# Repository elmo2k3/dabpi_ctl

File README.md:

# dabpi_ctl - RPi fm/fmhd/dab receiver control interface

![Image of DABPi+ v11 PCB]
(https://github.com/elmo2k3/dabpi_ctl/blob/master/doc/pics/dabpi+_v11.jpg)
DABPi+ for Raspberry Pi A+/B+ versions. Pi2 not tested yet.
![Image of DABPi v1 PCB]
(https://github.com/elmo2k3/dabpi_ctl/blob/master/doc/pics/dabpi_v1.jpg)
DABPi for older Raspberry Pi A/B versions.

## News

12.4.2015
Works on Pi2 now. New Kernel 3.18.11-v7+ included for Pi2.

## Warning

!!! Firmware files removed due to license issues !!!

This project is beta. A lot of features are still missing.

## Requirements

You need a RPi that has the option to mount the I2S extension header.
![Image of RPi with soldered I2S extension header]
(https://github.com/elmo2k3/dabpi_ctl/blob/master/doc/pics/IMG_0292.JPG)

Get the firmware package for Si4688 from Silabs.

Be sure to enable SPI in raspi-config.

Install wiringPi library. See http://wiringpi.com/download-and-install/

To get the audio you need to install a new kernel. It can be compiled from here
https://github.com/elmo2k3/linux or use the precompiled image. For the precompiled binarys, see the Install section.

## RPi A+/B+ instructions
![Image of RPi B+ with additional cables]
(https://github.com/elmo2k3/dabpi_ctl/blob/master/doc/pics/a_b_plus.jpg)

Connect P5 header pins 3,4,5 to GPIO header pins 12,35,38.

## Install

There is a very simple install script for a fresh raspian now (where there is nothing to be damaged).

```bash
wget https://github.com/elmo2k3/dabpi_ctl/raw/master/install_on_fresh_raspbian.sh
chmod a+x install_on_fresh_raspbian.sh
./install_on_fresh_raspbian.sh
```
This will install the commandline tool to /home/pi/dabpi_ctl

Unpack the firmware files (get it from silabs or ask me) into /home/pi/dabpi_ctl/firmware

### Manual Install

Get and compile the source code:

```bash
git clone https://github.com/elmo2k3/dabpi_ctl
cd dabpi_ctl
make
```
If you want to use the precompiled kernel, it can be found in the kernel/ directory.

```bash
sudo cp kernel/Image /boot/kernel.img
sudo rm -rf /lib/modules
sudo rm -rf /lib/firmware
sudo tar -C / -xvzf kernel/lib.tar.gz
```
Edit /etc/modules
```bash
bcm2708_dmaengine
snd-bcm2835
```
After a reboot load the module.

```bash
sudo modprobe snd-soc-rpi-dabpi
```
You should see this in the kernel log:
```bash
pi@raspberrypi ~/dabpi_ctl $ dmesg | tail -n1
[ 2435.067966] snd-dabpi snd-dabpi.0:  si468x-hifi <-> bcm2708-i2s.0 mapping ok
pi@raspberrypi ~/dabpi_ctl $
```

## Usage

Run dabpi_ctl:

```bash
[bjoern@x200 user_program]$ ./dabpi_ctl
usage: ./dabpi_ctl [-a|-b]
  -a             init DAB mode
  -b             init fm mode
  -c frequency   tune frequency in FM mode
  -d             fm status
  -e             dab status
  -f service     start service of dab service list
  -g             get dab service list
  -i channel     tune to channel in dab frequency list
  -j region      set frequency list
                    0   Baden-Wuertemberg
                    1   Bayern
                    2   Berlin-Brandenburg
                    3   Bremen
                    4   Hamburg
                    5   Hessen
                    6   Mecklenburg-Vorpommern
                    7   Niedersachsen
                    8   Nordrhein-Westfalen
                    9   Rheinland-Pfalz
                    10  Saarland
                    11  Sachsen
                    12  Sachsen-Anhalt
                    13  Schleswig-Holstein
                    14  Thueringen
                    15  Suedtirol (Italien)
                    16  Schweiz
  -k region      scan frequency list
  -l up|down     fm seek next station
  -m             fm rds status
  -n             dab get audio info
  -o             dab get subchannel info
  -s             get sys state (fm,dab,am...)
  -h             this help
```

### Audio output

To test audio output, redirect it from capture to playback device:

```bash
alsaloop -C hw:1,0
```
Stream audio to another linux machine over ssh:

```bash
ssh pi@PI-IP-ADDRESS 'arecord -D hw:1,0 -f dat -' | aplay -f dat -
```

### Examples

Enter fm mode:

```bash
pi@raspberrypi ~/dabpi_ctl $ sudo ./dabpi_ctl -b
si46xx_init_mode_fm()
si46xx_get_sys_state answer: 800000c001ff
si46xx_get_part_info answer: 800000c0000000005012000000005012000000000100
[...]
si46xx_fm_tune_freq(98500)
808000c0
pi@raspberrypi ~/dabpi_ctl $
```

Tune to radio station 106.700MHz:

```bash
pi@raspberrypi ~/dabpi_ctl $ sudo ./dabpi_ctl -c 106700
si46xx_fm_tune_freq(106700)
808000c0
pi@raspberrypi ~/dabpi_ctl $
```

Enter DAB mode and scan all channels in the list for NRW:

```bash
pi@raspberrypi ~/dabpi_ctl $ sudo ./dabpi_ctl -a -k 8
si46xx_init_mode_dab()
[...]
si46xx_dab_tune_freq(0): 818000c0
si46xx_dab_digrad_status(): Channel 0: ACQ: 1 RSSI: 45 SNR: -10 Name: DR Deutschland
si46xx_dab_tune_freq(1): 818000c0
si46xx_dab_digrad_status(): Channel 1: ACQ: 1 RSSI: 41 SNR: -10 Name: Radio fuer NRW
pi@raspberrypi ~/dabpi_ctl $
```

Select DAB channel:

```bash
pi@raspberrypi ~/dabpi_ctl $ sudo ./dabpi_ctl -i 1
si46xx_dab_tune_freq(0): 818000c0
pi@raspberrypi ~/dabpi_ctl $
```

Get ensemble information:

```bash
pi@raspberrypi ~/dabpi_ctl $ sudo ./dabpi_ctl -g
si46xx_dab_get_digital_service_list()
List size:     370
List version:  227
Services:      13
Num:  0  Service ID: e0d01005  Service Name: WDR-INFO          Component ID: 49162
                                                               Component ID: 49162
Num:  1  Service ID:     109d  Service Name: Domradio          Component ID: 12
                                                               Component ID: 0
Num:  2  Service ID: e0d01006  Service Name: WDR-TPEG          Component ID: 49163
                                                               Component ID: 0
Num:  3  Service ID:     d394  Service Name: WDR 4             Component ID: 14
                                                               Component ID: 0
Num:  4  Service ID:     df92  Service Name: VERA              Component ID: 8
                                                               Component ID: 0
Num:  5  Service ID:     d391  Service Name: 1LIVE             Component ID: 1
                                                               Component ID: 0
Num:  6  Service ID:     d395  Service Name: WDR 5             Component ID: 4
                                                               Component ID: 0
Num:  7  Service ID:     d496  Service Name: FUNKHAUS EUROPA   Component ID: 5
                                                               Component ID: 0
Num:  8  Service ID: e0d01004  Service Name: WDR-EPG           Component ID: 49161
                                                               Component ID: 0
Num:  9  Service ID:     df95  Service Name: KinderRadioKanal  Component ID: 2
                                                               Component ID: 0
Num: 10  Service ID:     df91  Service Name: 1LIVE diggi       Component ID: 3
                                                               Component ID: 0
Num: 11  Service ID:     1462  Service Name: RADIO IMPALA      Component ID: 13
                                                               Component ID: 0
Num: 12  Service ID:     d392  Service Name: WDR 2             Component ID: 7
                                                               Component ID: 0
pi@raspberrypi ~/dabpi_ctl $
```

Start one of the services in ensemble:

```bash
pi@raspberrypi ~/dabpi_ctl $ sudo ./dabpi_ctl -f 5
si46xx_dab_get_digital_service_list()
List size:     370
List version:  227
Services:      13
Num:  0  Service ID: e0d01005  Service Name: WDR-INFO          Component ID: 49162
                                                               Component ID: 49162
[...]
Starting service 1LIVE            d391 1
pi@raspberrypi ~/dabpi_ctl $
```

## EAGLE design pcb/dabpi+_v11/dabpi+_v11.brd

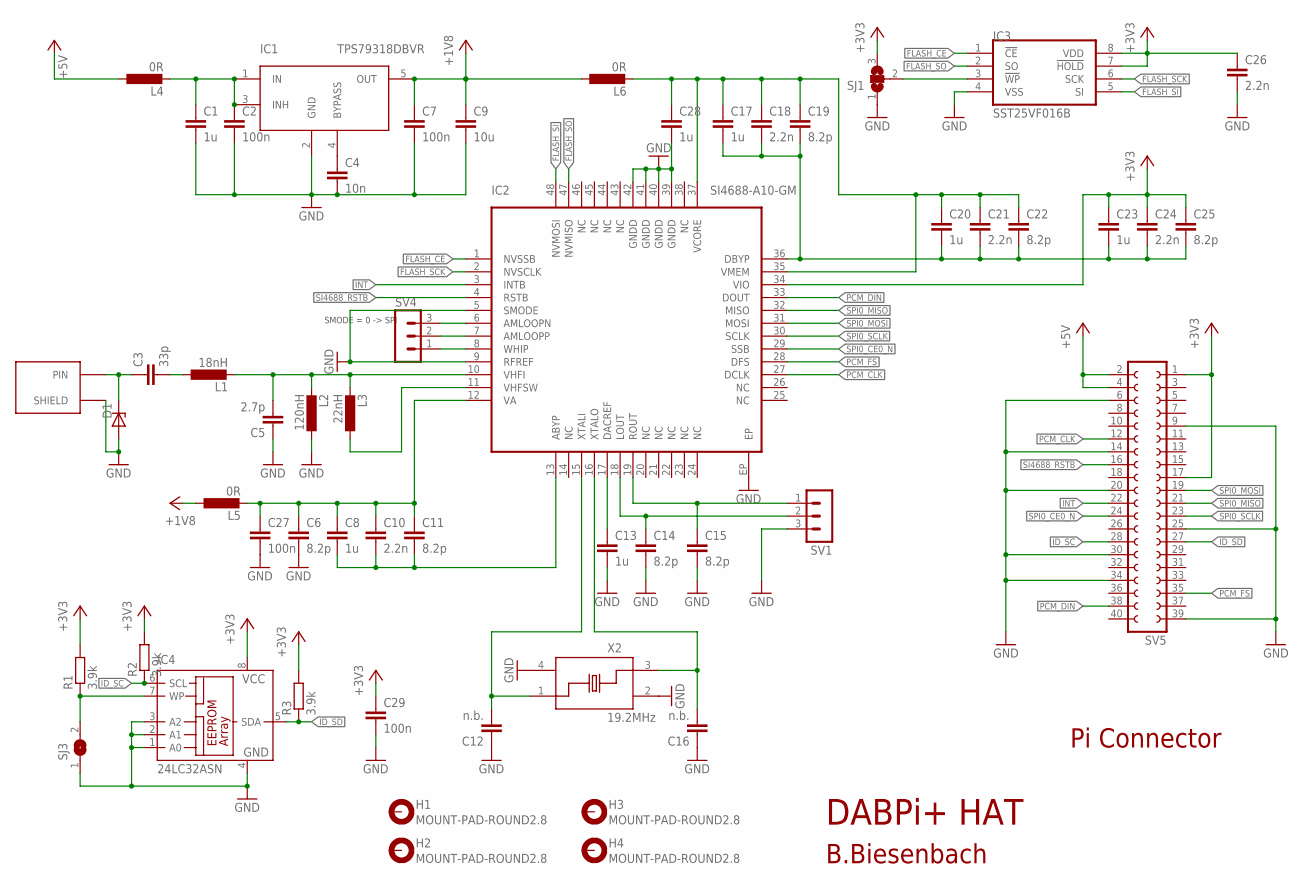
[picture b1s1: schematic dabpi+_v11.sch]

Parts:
C1, C8, C13, C17, C20, C23, C28: 1u; SMD0603
C2, C7, C27, C29: 100n; SMD0603
C3: 33p; SMD0402
C4: 10n; SMD0603
C5: 2.7p; SMD0402
C6, C11, C14, C15, C19, C22, C25: 8.2p; SMD0603
C9: 10u; SMD0603
C10, C18, C21, C24, C26: 2.2n; SMD0603
C12, C16: n.b.; SMD0402
D1: ESD9L5.0; SOD923
H1, H2, H3, H4: MOUNT-PAD-ROUND2.8; 2,8-PAD
IC1: TPS79318DBVR; SOT23-5
IC2: SI4688-A10-GM; QFN48
IC3: SST25VF016B; SO08
IC4: 24LC32ASN; SO-08
L1: 18nH; SMD0402
L2: 120nH; SMD0402
L3: 22nH; SMD0402
L4, L5, L6: 0R; SMD0603
R1, R2, R3: 3.9k; SMD0603
SJ1: SJ2W; SJ_2
SJ3: SJ
SV1, SV4: MA03-1
SV5: FE20-2
X1: SMA_LP_1.57MM
X2: 19.2MHz; XTAL_3.2X2.5

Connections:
+1V8: C7.1, C9.1, IC1.5 (OUT), L5.1, L6.1
+3V3: C23.1, C24.1, C25.1, C26.1, C29.1, IC2.34 (VIO), IC3.7 (!HOLD), IC3.8 (VDD), IC4.8 (VCC), R1.2, R2.2, R3.2, SJ1.3, SV5.1, SV5.17
+5V: L4.1, SV5.2, SV5.4
FLASH_CE: IC2.1 (NVSSB), IC3.1 (!CE)
FLASH_SCK: IC2.2 (NVSCLK), IC3.6 (SCK)
FLASH_SI: IC2.48 (NVMOSI), IC3.5 (SI)
FLASH_SO: IC2.47 (NVMISO), IC3.2 (SO)
GND: C1.2, C2.2, C4.2, C5.1, C6.2, C7.2, C9.2, C12.1, C13.2, C14.2, C15.2, C16.1, C26.2, C27.2, C28.2, C29.2, D1.A, IC1.2 (GND), IC2.5 (SMODE), IC2.9 (RFREF), IC2.39 (GNDD), IC2.40 (GNDD), IC2.41 (GNDD), IC2.42 (GNDD), IC2.EP, IC3.4 (VSS), IC4.1 (A0), IC4.2 (A1), IC4.3 (A2), IC4.4 (GND), L2.1, SJ1.1, SJ3.1, SV1.3, SV5.6, SV5.9, SV5.14, SV5.20, SV5.25, SV5.30, SV5.34, SV5.39, X1.GND (SHIELD), X1.GND@1 (SHIELD), X1.GND@2 (SHIELD), X1.GND@3 (SHIELD), X2.2 (GND), X2.4 (GND)
ID_SC: IC4.6 (SCL), R2.1, SV5.28
ID_SD: IC4.5 (SDA), R3.1, SV5.27
INT: IC2.3 (INTB), SV5.22
LDO_IN: C1.1, C2.1, IC1.1 (IN), IC1.3 (INH), L4.2
unnamed: C3.2, L1.1
unnamed: C5.2, IC2.10 (VHFI), L1.2, L2.2, L3.2
unnamed: IC2.11 (VHFSW), L3.1
unnamed: C8.2, C10.2, C11.2, IC2.13 (ABYP)
unnamed: C17.2, C18.2, C19.2, C20.2, C21.2, C22.2, C23.2, C24.2, C25.2, IC2.36 (DBYP)
unnamed: C12.2, IC2.15 (XTALI), X2.1
unnamed: C16.2, IC2.16 (XTALO), X2.3
unnamed: C13.1, IC2.17 (DACREF)
unnamed: IC3.3 (!WP), SJ1.2
unnamed: C4.1, IC1.4 (BYPASS)
unnamed: C6.1, C8.1, C10.1, C11.1, C27.1, IC2.12 (VA), L5.2
unnamed: IC2.6 (AMLOOPN), SV4.3
unnamed: C17.1, C18.1, C19.1, C20.1, C21.1, C22.1, C28.1, IC2.35 (VMEM), IC2.37 (VCORE), L6.2
unnamed: IC2.7 (AMLOOPP), SV4.2
unnamed: IC2.8 (WHIP), SV4.1
unnamed: IC4.7 (WP), R1.1, SJ3.2
PCM_CLK: IC2.27 (DCLK), SV5.12
PCM_DIN: IC2.33 (DOUT), SV5.38
PCM_FS: IC2.28 (DFS), SV5.35
RF_IN: C3.1, D1.K (C), X1.PIN
SI4688_LOUT: C14.1, IC2.18 (LOUT), SV1.2
SI4688_ROUT: C15.1, IC2.19 (ROUT), SV1.1
SI4688_RSTB: IC2.4 (RSTB), SV5.16
SPI0_CE0_N: IC2.29 (SSB), SV5.24
SPI0_MISO: IC2.32 (MISO), SV5.21
SPI0_MOSI: IC2.31 (MOSI), SV5.19
SPI0_SCLK: IC2.30 (SCLK), SV5.23

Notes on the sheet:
DABPi+ HAT
SMODE = 0 -> SPI
Pi Connector
B.Biesenbach

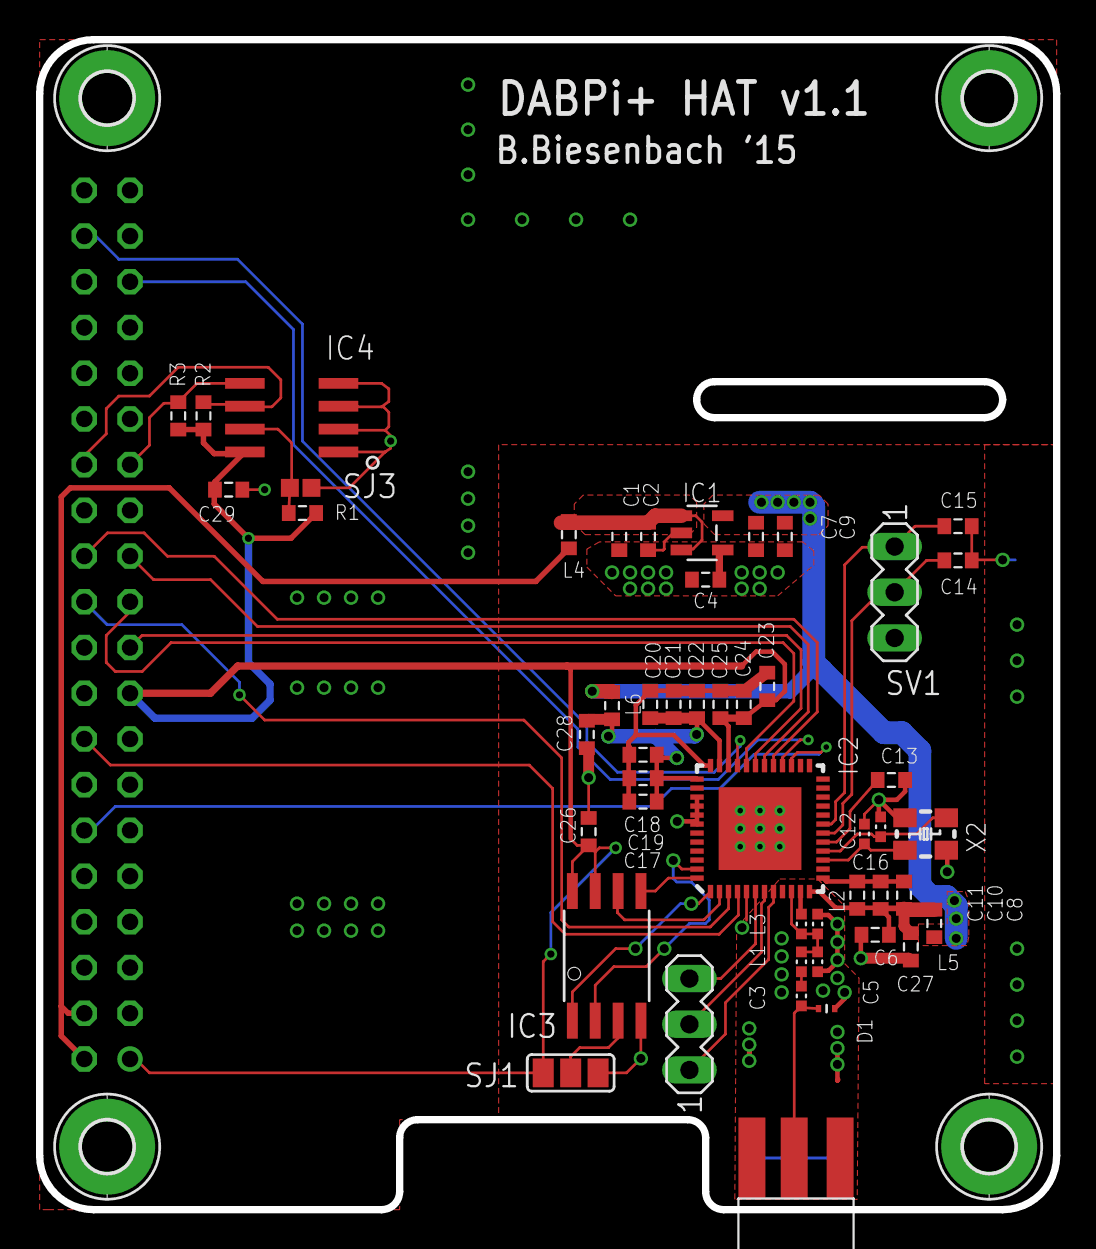
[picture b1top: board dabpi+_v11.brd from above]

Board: 2 copper layers, 56.5 x 65.0 mm, 54 parts (1 on the bottom side), 39 nets.

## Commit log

2014-08-19 Support for multi component services
    Added two hardcoded frequency lists for NRW and Bayern
2014-08-20 complete frequency list for germany added
2014-08-20 si46xx_dab_scan implemented
2014-08-20 fixed helptext
2014-08-20 dab_get_ensemble_info() shows ensemble name now
2014-08-20 version name added
2014-08-20 README.md some more examples
2014-08-21 fm seek up/down implemented
2014-08-22 rds parsing first steps
2014-08-25 some more rds parsing
2014-08-25 service list gets sorted by service_id
2014-08-25 simple install script
    very simple script to install wiringPi, dabpi_ctl
    and the new kernel on a fresh raspbian
2014-08-25 readme updated install script section
2014-08-26 Firmware files removed
2014-08-27 pic of rpi with i2s header added
2014-08-27 readme pic of rpi added, example to test audio output
2014-08-27 picture of pcb added
2014-08-27 pcb: schematic and board added
2014-08-28 known bugs file added
2014-08-29 dab_get_subchannel_info()
    thanks to Wolfgang Mölter
2014-08-30 read now waits for command complete
    timeout in si46xx_read added
    dab_get_audio_info improvements by Wolfgang Mölter
2014-10-27 added bill of material
2014-11-12 Added support for Italian radio stations in Suedtirol
2014-11-25 modified FE_VARM/B values to improve sensitivity
2014-11-27 Added new ignore file
2014-11-27 Code reformatting
2014-11-27 modified FE_VARM/B values to improve sensitivity
    New values from Bjoern
2014-11-27 Rewritten complete automatic install program
    !! -- Very important notes -- !!
    This program is rewriting the "raspi-blacklist.conf" and "modules" file!
    If you have any changes made to them before you have to remember to
    recode them after installation has finished!
    This software is making backups of all files touched to your home
    directory!
2014-12-18 readme.md: no a+/b+ support and small fix for script install
2014-12-21 install script fix for permission issues when not run as root
2014-12-21 added info for a+/b+ support
2014-12-21 readme info about firmware and streaming over ssh
2015-02-04 pcb layout updates
    added board dabpi+ for RPi B+, updated dabpi board
    both boards are now prepared for si4689
2015-03-22 New DABPi+ version 1.1 added
2015-03-22 Fixed wrong linux kernel src link
2015-03-22 dabpi+ v11 image added
2015-03-22 readme changes
2015-03-29 first am implementation (si4689)
2015-03-29 Command to get sys state added
2015-04-12 Kernel 3.18.11-v7+ and modules for Pi2
2015-04-12 Typo in install script fixed
2015-04-12 Channel for Sachsen corrected
    Thanks to Dirk
2015-04-12 readme new news section
2015-04-14 Kernel image for Pi1 updated to 3.18.11
2015-05-03 Added dabpi+_v11 schematic pdf
2015-05-09 Channel 12A added for Bremen
    Tnx to 900ss
2015-10-26 Kernel image 4.1.11+ added and modules updated
2015-11-12 Channels for Switzerland added
